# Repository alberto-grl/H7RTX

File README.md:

https://www.youtube.com/watch?v=FsxwJKLU6Ns&ab_channel=AlbertoGarlassi

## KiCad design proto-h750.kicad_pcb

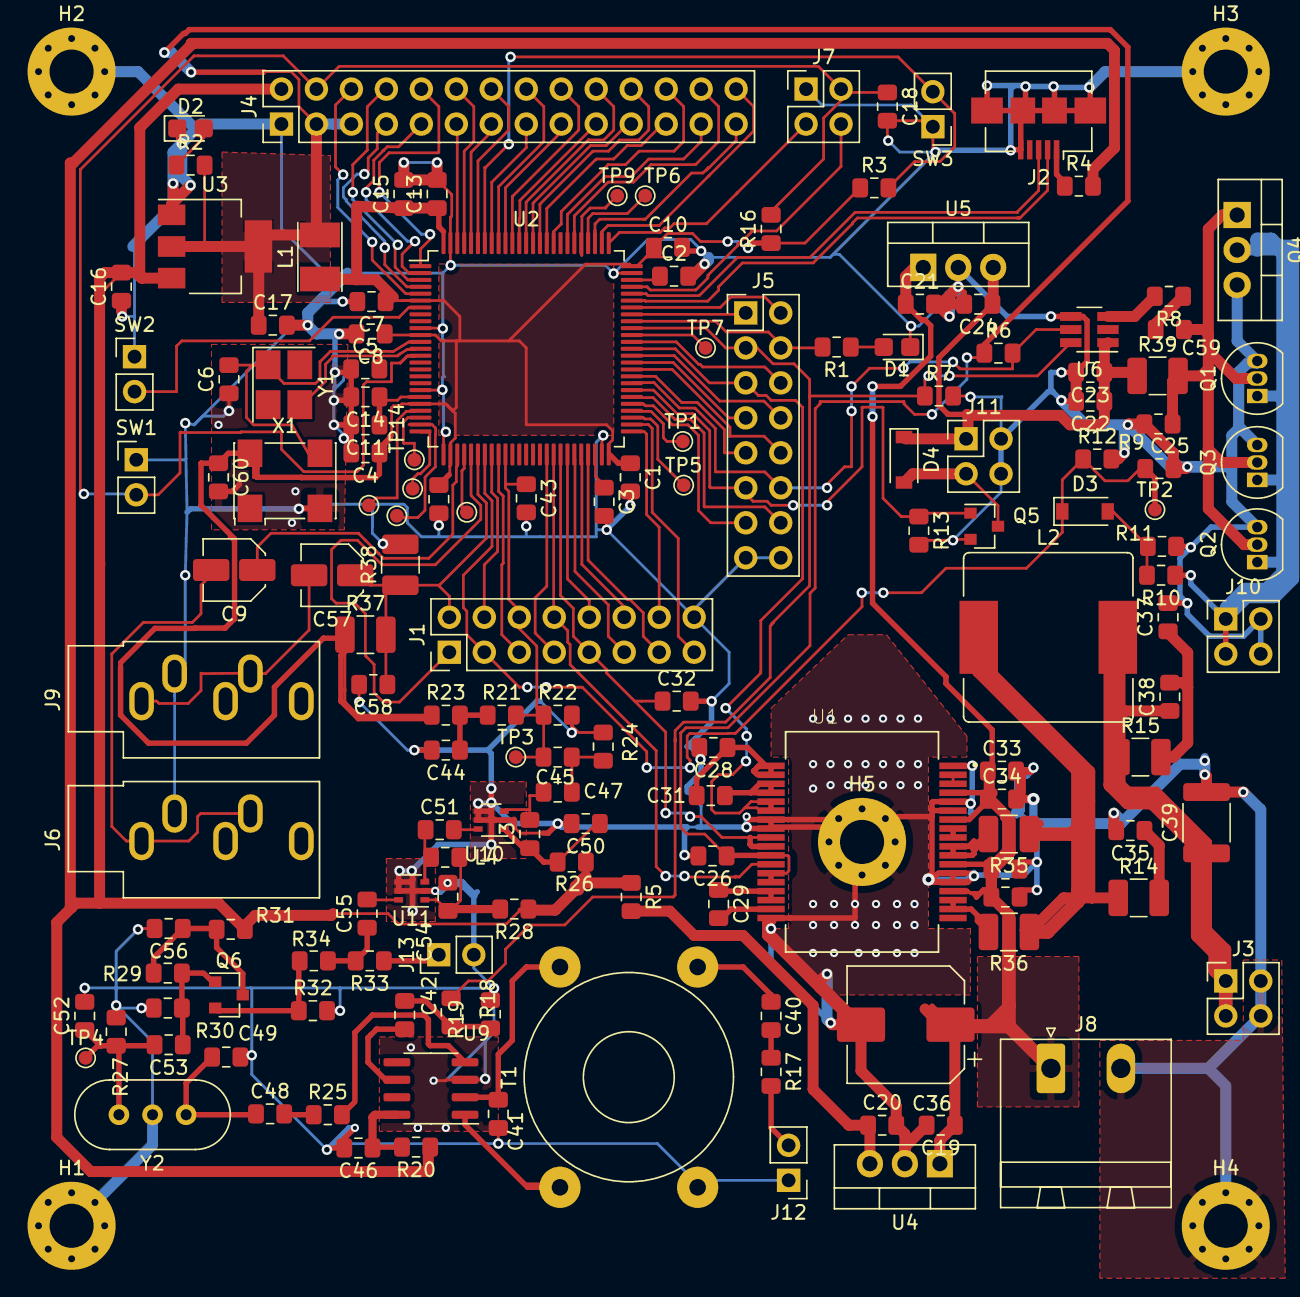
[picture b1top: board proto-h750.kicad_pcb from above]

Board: 4 copper layers, 160 parts (0 on the bottom side), 130 nets.

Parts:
C1, C2, C3, C4, C7, C8, C10, C12, C13, C14, C18, C23, C24, C26, C28, C29, C31, C32, C37, C38, C44, C45, C46, C47, C50, C54, C56, C60: 100n; C_0805_2012Metric_Pad1.15x1.40mm_HandSolder
C5, C6: 18p; C_0805_2012Metric_Pad1.15x1.40mm_HandSolder
C9, C57: 10u; C_Elec_4x5.4
C11, C22, C30, C34: 1u; C_0805_2012Metric_Pad1.15x1.40mm_HandSolder
C15: 4.7u; C_0805_2012Metric_Pad1.15x1.40mm_HandSolder
C16, C17, C19, C20, C21: 10u; C_0805_2012Metric_Pad1.15x1.40mm_HandSolder
C25, C40, C42, C48, C51, C53, C55: 10n; C_0805_2012Metric_Pad1.15x1.40mm_HandSolder
C27, C33: 220n; C_0805_2012Metric_Pad1.15x1.40mm_HandSolder
C35: 330p; C_0805_2012Metric_Pad1.15x1.40mm_HandSolder
C36: 220u; CP_Elec_8x10
C39: 220n polyester; C_1812_4532Metric_Pad1.30x3.40mm_HandSolder
C41, C59: C; C_0805_2012Metric_Pad1.15x1.40mm_HandSolder
C43: 10p; C_0805_2012Metric_Pad1.15x1.40mm_HandSolder
C49, C52: 0; C_0805_2012Metric_Pad1.15x1.40mm_HandSolder
C58: 1n; C_0805_2012Metric_Pad1.15x1.40mm_HandSolder
D1, D2: RED; LED_0805_2012Metric_Castellated
D3: D; D_SOD-123
D4: MMBD914LT3G; D_SOD-123
H1, H2, H3, H4, H5: MountingHole_Pad; MountingHole_3.2mm_M3_Pad_Via
J1, J5: Conn_02x08_Odd_Even; PinHeader_2x08_P2.54mm_Vertical
J2: USB_B_Micro; USB_Micro-B_Amphenol_10104110_Horizontal
J3, J7, J10, J11: Conn_02x02_Odd_Even; PinHeader_2x02_P2.54mm_Vertical
J4: Conn_02x14_Odd_Even; PinHeader_2x14_P2.54mm_Vertical
J6, J9: AudioJack3; Jack_3.5mm_CUI_SJ1-3535NG_Horizontal
J8: Screw_Terminal_01x02; PhoenixContact_MSTBA_2,5_2-G-5,08_1x02_P5.08mm_Horizontal
J12, J13: Conn_01x02; PinHeader_1x02_P2.54mm_Vertical
L1: NRH3012T100MN; L_Taiyo-Yuden_NR-30xx_HandSoldering
L2: 47u SRR1210-470M; L_Bourns_SRR1210A
L3, L4: 10u; L_0805_2012Metric_Pad1.15x1.40mm_HandSolder
Q1, Q2, Q3: BS170; TO-92_Inline
Q4: IRF540N; TO-220-3_Vertical
Q5: BSS138; SOT-23
Q6: MMBT2222; SOT-23
R1, R2: 220R; R_0805_2012Metric_Pad1.15x1.40mm_HandSolder
R3, R13, R16: 10K; R_0805_2012Metric_Pad1.15x1.40mm_HandSolder
R4, R5, R17, R25, R33, R34: 0; R_0805_2012Metric_Pad1.15x1.40mm_HandSolder
R6, R7, R10, R12, R18, R21, R22: 10k; R_0805_2012Metric_Pad1.15x1.40mm_HandSolder
R8: 2.2; R_0805_2012Metric_Pad1.15x1.40mm_HandSolder
R9: 1K; R_0805_2012Metric_Pad1.15x1.40mm_HandSolder
R11: 330; R_0805_2012Metric_Pad1.15x1.40mm_HandSolder
R14: 20 0.25W; R_1210_3225Metric_Pad1.42x2.65mm_HandSolder
R15: 6.2 0.25 W; R_1210_3225Metric_Pad1.42x2.65mm_HandSolder
R19: 3k3; R_0805_2012Metric_Pad1.15x1.40mm_HandSolder
R20, R23, R26, R28, R31: 100; R_0805_2012Metric_Pad1.15x1.40mm_HandSolder
R24, R27: 100k; R_0805_2012Metric_Pad1.15x1.40mm_HandSolder
R29: 62k; R_0805_2012Metric_Pad1.15x1.40mm_HandSolder
R30: 150k; R_0805_2012Metric_Pad1.15x1.40mm_HandSolder
R32: 2k2; R_0805_2012Metric_Pad1.15x1.40mm_HandSolder
R35, R36: 0; R_1210_3225Metric_Pad1.42x2.65mm_HandSolder
R37, R38, R39: 10k; R_1210_3225Metric_Pad1.42x2.65mm_HandSolder
SW1, SW2, SW3: SW_DIP_x01; PinHeader_1x02_P2.54mm_Vertical
T1: Transformer_1P_1S; Transformer_Toroid_Horizontal_D14.0mm_Amidon-T50
TP1, TP2, TP3, TP4, TP5: TestPoint; TestPoint_Pad_D1.0mm
TP6, TP7, TP9, TP13, TP14, TP15, TP16, TP17: TestPoint_Small; TestPoint_Pad_D1.0mm
U1: STA516BETR; SOP65P1420X343-36N
U2: STM32H750VBT6; LQFP-100_14x14mm_P0.5mm
U3: AP1117-33; SOT-223-3_TabPin2
U4: LM7805_TO220; TO-220-3_Vertical
U5: LM7812_TO220; TO-220-3_Vertical
U6: LM5134AMF_NOPB; SOT-23-6_Handsoldering
U9: SA612; SOIC-8_3.9x4.9mm_P1.27mm
U10, U11: BGA2869; SOT-363_SC-70-6
X1: ASV-xxxMHz; Oscillator_SMD_Abracon_ASV-4Pin_7.0x5.1mm
Y1: 16MHz; Crystal_SMD_3225-4Pin_3.2x2.5mm_HandSoldering
Y2: ECS-10.7-7.5B; Crystal_HC49-U-3Pin_Vertical

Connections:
+5V: C16.2, J4.2, R4.2, R5.1, R20.1, R26.1, R28.1, R31.1, U3.3
+24V: C19.1, C21.1, C27.1, C30.1, C33.1, C34.1, C36.1, J8.1, U1.4, U1.7, U1.12, U1.15, U4.1, U5.1
/AudioOut: C9.1, U2.28
/BOOT: R3.2, SW3.2, U2.94
/Microphone: C57.1, C58.1, J1.2, R37.2, R38.1, U2.31
/PA0: TP13.1, U2.22
/PA1: TP14.1, U2.23
/PA2: TP15.1, U2.24
/PA3: TP16.1, U2.25
/PA5: TP17.1, U2.29
/PA6: J1.1, U2.30
/PA8: J5.4, R1.2, U2.67
/PA9: J5.1, U2.68
/PA10: J5.2, U2.69
/PA15: J4.28, U2.77
/PB0: J1.5, U2.34
/PB3: J4.19, U2.89
/PB4: J4.18, U2.90
/PB5: J4.17, U2.91
/PB6: J4.16, U2.92
/PB7: J4.15, U2.93
/PB8: J4.14, U2.95
/PB9: J4.13, U2.96
/PB10: J1.12, U2.46
/PB11: J1.13, U2.47
/PB12: J1.14, U2.51
/PB13: J1.15, U2.52
/PC5: J1.4, U2.33
/PC7: J5.6, U2.64
/PC10: J4.27, U2.78
/PC13: SW2.2, U2.7
/PD0: J4.26, U2.81
/PD1: J4.25, U2.82
/PD3: J4.24, U2.84
/PD4: J4.23, U2.85
/PD5: J4.22, U2.86
/PD6: J4.21, U2.87
/PD7: J4.20, U2.88
/PD8: J5.13, U2.55
/PD9: J5.14, U2.56
/PD12: J5.9, U2.59
/PD13: J5.10, U2.60
/PD14: J5.7, U2.61
/PD15: J5.8, U2.62
/PE0: J4.12, U2.97
/PE1: J4.11, U2.98
/PE2: J4.10, U2.1
/PE3: J4.9, U2.2
/PE4: J4.8, U2.3
/PE5: J4.7, U2.4
/PE6: J4.6, U2.5
/PE11: J1.7, U2.41
/PE14: J1.10, U2.44
/PE15: J1.11, U2.45
/SD_CK: TP9.1, U2.80
/SD_D0: TP7.1, U2.65
/SWCLK: J7.3, U2.76
/SWDIO: J7.4, U2.72
/TX/+12V: C22.1, C23.1, C24.1, D4.1, J11.1, R39.1, U5.3, U6.1
/USB0_D+: TP1.1, U2.54
/USB0_D-: TP5.1, U2.53
/USB1_D+: J2.3, U2.71
/USB1_D-: J2.2, U2.70
/nCS: TP6.1, U2.79
/nRESET: C18.1, J4.4, J7.2, R16.2, SW1.2, U2.14
A_FAULT: C32.1, J1.9, U1.27, U1.28, U2.43
A_PWM: J5.5, U1.31, U1.32, U2.63
A_PWRDN: J1.8, U1.25, U2.42
GND: C1.2, C2.2, C3.2, C4.2, C5.1, C6.1, C7.2, C8.2, C10.2, C11.2, C12.2, C13.2, C14.2, C15.2, C16.1, C17.2, C18.2, C19.2, C20.2, C21.2, C22.2, C23.2, C24.2, C25.2, C26.2, C27.2, C28.2, C30.2, C32.2, C33.2, C34.2, C35.2, C36.2, C37.2, C39.2, C41.2, C43.2, C44.2, C46.2, C49.2, C50.2, C52.2, C54.2, C56.2, C58.2, C60.2, D1.1, D2.1, H1.1, H2.1, H3.1, H4.1, H5.1, J1.16, J2.5, J2.6, J3.2, J3.4, J4.1, J5.15, J5.16, J6.T, J7.1, J8.2, J9.T, J10.2, J10.4, J11.2, J11.4, J12.1, J13.2, Q1.3, Q2.3, Q3.3, Q4.3, Q5.2, R7.2, R9.2, R11.2, R12.2, R13.2, R19.2, R22.2, R24.2, R27.2, R30.2, R32.2, R38.2, SW1.1, SW2.1, SW3.1, T1.1, U1.1, U1.5, U1.6, U1.13, U1.14, U1.19, U1.29, U1.30, U2.10, U2.19, U2.26, U2.49, U2.74, U2.99, U3.1, U4.2, U5.2, U6.4, U9.3, U10.2, U10.4, U10.5, U11.2, U11.4, U11.5, X1.2, Y2.2
MCO: J5.3, R7.1, R18.1, U2.66, U6.6
MODUL_OUT: C38.1, C39.1, J3.1, J3.3, L2.2, R15.1
unnamed: C2.1, U2.73
unnamed: C3.1, U2.48
unnamed: C5.2, U2.13, Y1.3
unnamed: C6.2, U2.12, X1.3, Y1.1
unnamed: C9.2, J6.R, J6.S
unnamed: C11.1, C14.1, U2.20
unnamed: C20.1, R5.2, U4.3
unnamed: C28.1, C31.1, U1.35, U1.36
unnamed: C29.1, U1.21, U1.22
unnamed: C29.2, U1.20
unnamed: C31.2, U1.33, U1.34
unnamed: C35.1, R14.2
unnamed: C37.1, C38.2, R15.2
unnamed: C40.1, T1.2
unnamed: C40.2, R17.1
unnamed: C41.1, T1.4, U9.2
unnamed: C42.1, U9.6
unnamed: C42.2, R18.2, R19.1
unnamed: C44.1, R21.1, R23.2
unnamed: C45.1, C47.2, R24.1
unnamed: C46.1, R20.2, U9.8
unnamed: C47.1, L3.2, U10.3
unnamed: C48.1, C49.1, Y2.1
unnamed: C48.2, R25.1
unnamed: C50.1, L3.1, R26.2, U10.1
unnamed: C51.1, L4.2, U11.3
unnamed: C51.2, U10.6
unnamed: C52.1, C53.2, R27.1, TP4.1, Y2.3
unnamed: C53.1, Q6.1, R29.2, R30.1
unnamed: C54.1, L4.1, R28.2, U11.1
unnamed: C55.1, R33.2, R34.1
unnamed: C55.2, U11.6
unnamed: C56.1, Q6.3, R29.1, R31.2
unnamed: C57.2, J9.R, J9.S
unnamed: C59.1, Q1.2, Q2.2, Q3.2, Q4.1, R9.1, R39.2
unnamed: C59.2, R8.1
unnamed: D1.2, R1.1
unnamed: D2.2, R2.1
unnamed: D3.2, R10.2, R11.1
unnamed: D4.2, J11.3, Q5.3
unnamed: J2.1, R4.1
unnamed: J10.1, J10.3, Q1.1, Q2.1, Q3.1, Q4.2, R10.1
unnamed: J12.2, R17.2
unnamed: J13.1, R33.1
unnamed: L2.1, R14.1, R35.1, R36.1
unnamed: Q6.2, R32.1, R34.2
unnamed: R8.2, U6.3
unnamed: R25.2, U9.4
unnamed: R35.2, U1.10, U1.11
unnamed: R36.2, U1.16, U1.17
unnamed: T1.3, U9.1
unnamed: U1.2, U1.3
unnamed: U1.8, U1.9
RF_ADC_IN: C43.1, C45.2, J1.6, R21.2, R22.1, TP3.1, U2.35
RXTX: J5.11, Q5.1, R13.1, U2.57
TXV: C25.1, D3.1, J1.3, R12.1, TP2.1, U2.32
TX_ENA: J5.12, R6.2, U2.58, U6.5
VCC: C17.1, C26.1, J4.3, J4.5, L1.2, R2.2, R6.1, U1.23, U1.24, U1.26, U3.2
VCC_CPU: C1.1, C4.1, C7.1, C8.1, C10.1, C12.1, C13.1, C15.1, C60.1, L1.1, R3.1, R16.1, R23.1, R37.1, U2.6, U2.11, U2.21, U2.27, U2.50, U2.75, U2.100, X1.4

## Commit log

2020-11-01 Start
2020-11-03 Added sheet 2
2020-11-05 Added symbol for SA612
2020-11-05 SA612 + emitter follower
2020-11-06 Some progress
2020-11-11 Started TX
2020-11-12 More TX
2020-12-01 Before annotating
2020-12-20 Before deleting Flash
2020-12-21 More routing
2020-12-21 RX placed
2020-12-22 RX routed
2021-01-11 More rouiting
2021-01-12 Almost routed
2021-01-13 All tracks routed
    DRC to be cleared
2021-01-13 DRC OK
2021-01-13 DRC OK 2
2021-01-14 Some pouring
2021-01-15 Better MMIC DC link
    To be done on other
